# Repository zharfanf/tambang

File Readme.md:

Pada kode di folder sim_modul_arduino terdapat beberapa kode yang dapat diubah untuk menyesuaikan dengan kebutuhan. Bagian kode yang dimaksud adalah pada bagian Editables

1. Variabel minutes adalah variabel yang menyatakan seberapa lama notifikasi akan dikirimkan ulang (dalam satuan milisekon) apabila tangki belum dibersihkan setelah notifikasi pertama muncul. Nilai default dan maksimal adalah 30 detik. Disarankan untuk tidak mengubah nilai tersebut yang bisa berakibat pada errornya kode.

2. Variabel telpNumber adalah variabel yang menyimpan nomor telepon yang ingin dikirimkan notifikasi

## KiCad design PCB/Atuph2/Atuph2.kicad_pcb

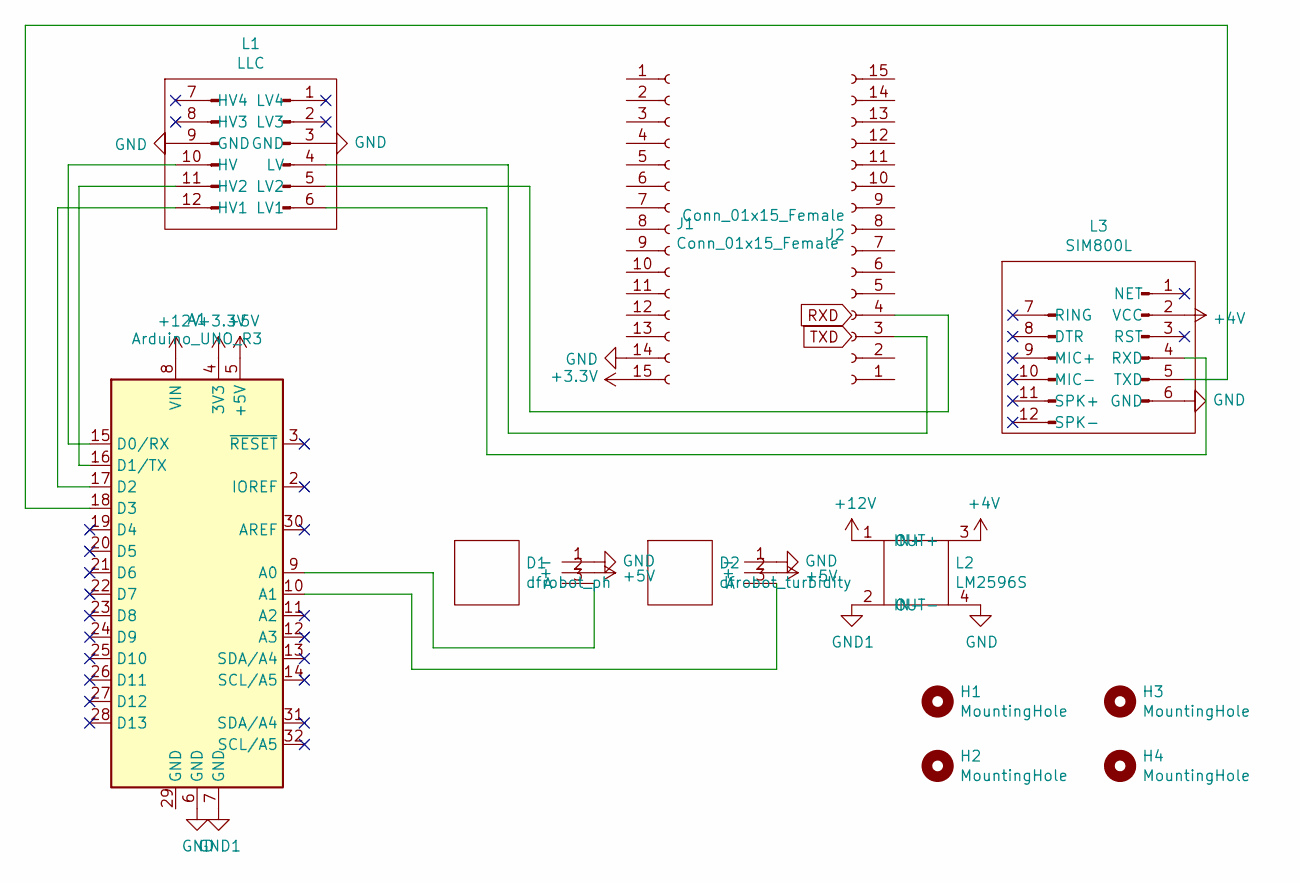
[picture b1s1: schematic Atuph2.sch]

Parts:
A1: Arduino_UNO_R3; Arduino
D1: dfrobot_ph
D2: dfrobot_turbidity
H1, H2, H3, H4: MountingHole; MountingHole_3mm_Pad
J1, J2: Conn_01x15_Female; PinSocket_1x15_P2.54mm_Vertical
L1: LLC
L2: LM2596S
L3: SIM800L

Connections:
+3V3: A1.4 (3V3), J1.15
+4V: L2.3 (OUT+), L3.2 (VCC)
+5V: A1.5 (+5V), D1.2 (+), D2.2 (+)
+12V: A1.8 (VIN), L2.1 (IN+)
GND: A1.6 (GND), D1.1 (-), D2.1 (-), J1.14, L1.3 (GND), L1.9 (GND), L2.4 (OUT-), L3.6 (GND)
GND1: A1.7 (GND), L2.2 (IN-)
unnamed: A1.9 (A0), D1.3 (A)
unnamed: A1.10 (A1), D2.3 (A)
unnamed: A1.15 (D0/RX), L1.10 (HV)
unnamed: A1.16 (D1/TX), L1.11 (HV2)
unnamed: A1.17 (D2), L1.12 (HV1)
unnamed: A1.18 (D3), L3.5 (TXD)
unnamed: J2.3, L1.4 (LV)
unnamed: J2.4, L1.5 (LV2)
unnamed: L1.6 (LV1), L3.4 (RXD)

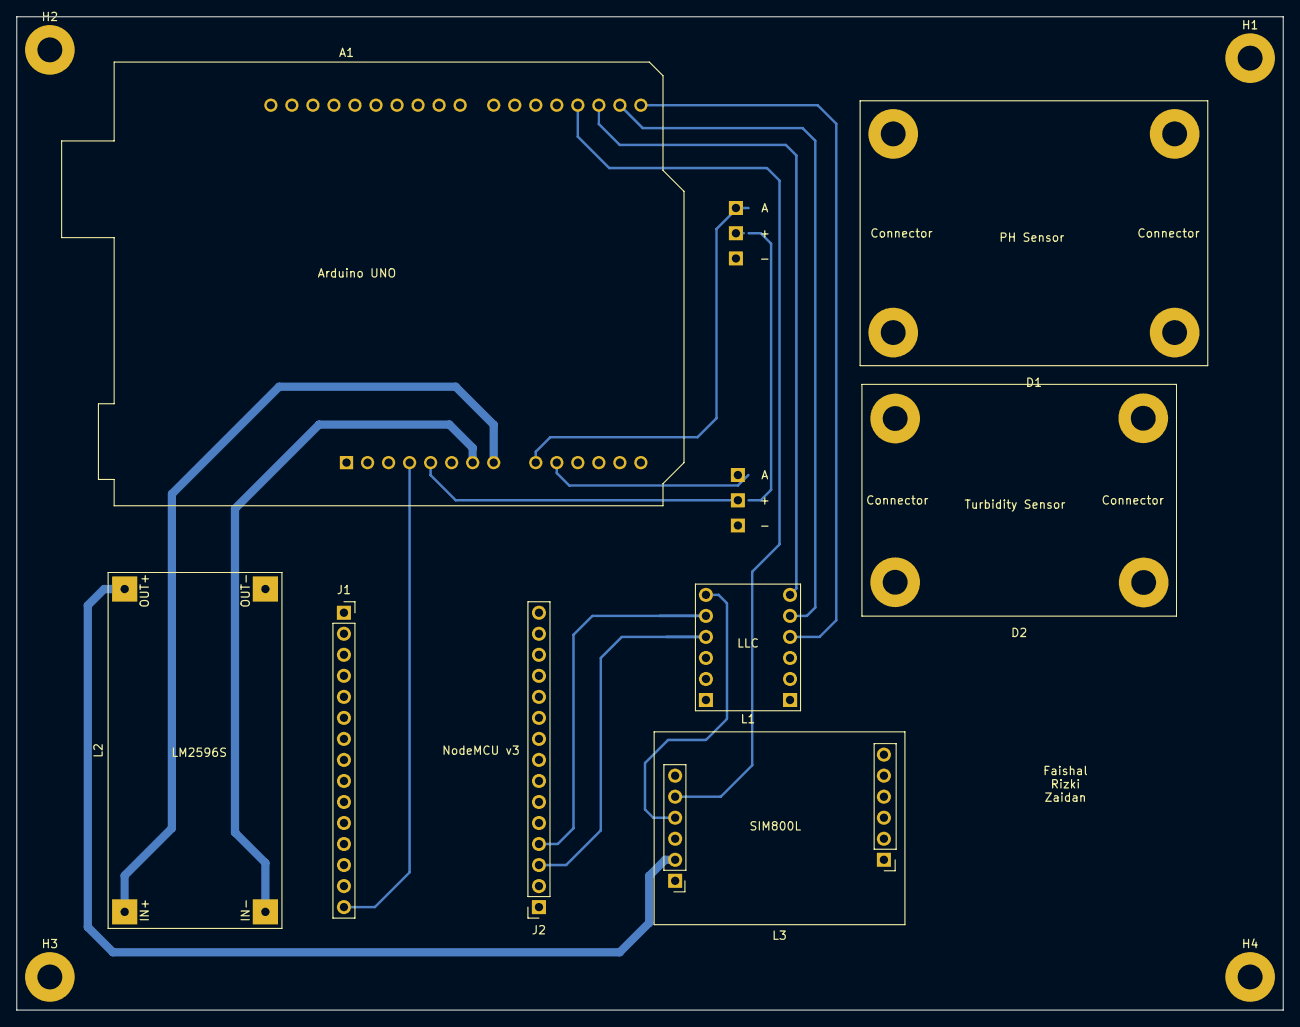
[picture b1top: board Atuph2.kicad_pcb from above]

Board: 2 copper layers, 153.0 x 120.0 mm, 12 parts (0 on the bottom side), 15 nets.

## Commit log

2022-01-11 Tambah kurawal
2022-01-11 adding 5 minutes interval
2022-01-11 merging sim module to main program
2022-01-11 adding abs func to handle rollover scenario
2022-01-12 add PCB design
2022-01-13 change PCB trace width
2022-01-13 change nodeMCU in layout v2 to amica
2022-01-13 add track
2022-01-19 Refactoring Code
2022-01-19 Adding Readme.md
2022-01-21 tambah turbidity
2022-01-21 merging tds to main code
2022-01-21 fixing bug
2022-01-21 changing turbidity to tds
2022-01-21 blm bisa
2022-01-23 fixing error
2022-01-23 TDS aman
2022-01-26 Adding a feature when the difference of two timers is zero
2022-01-26 cleaning the code
2022-01-26 fixing the Bug
2022-01-26 Adding Documentation
2022-01-29 updating AP name
2022-01-29 Fixing syntax error
2022-01-29 changing logic sequence
2022-01-29 fixing bug?
2022-01-29 fixing bugs(2)
2022-01-29 fixing bugs(3)
2022-01-29 siap dikirim
2022-01-30 Revising the documentation
